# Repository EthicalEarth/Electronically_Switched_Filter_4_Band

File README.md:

This filter based on construction pu2clr from https://github.com/pu2clr/auto_bpf_arduino/ .

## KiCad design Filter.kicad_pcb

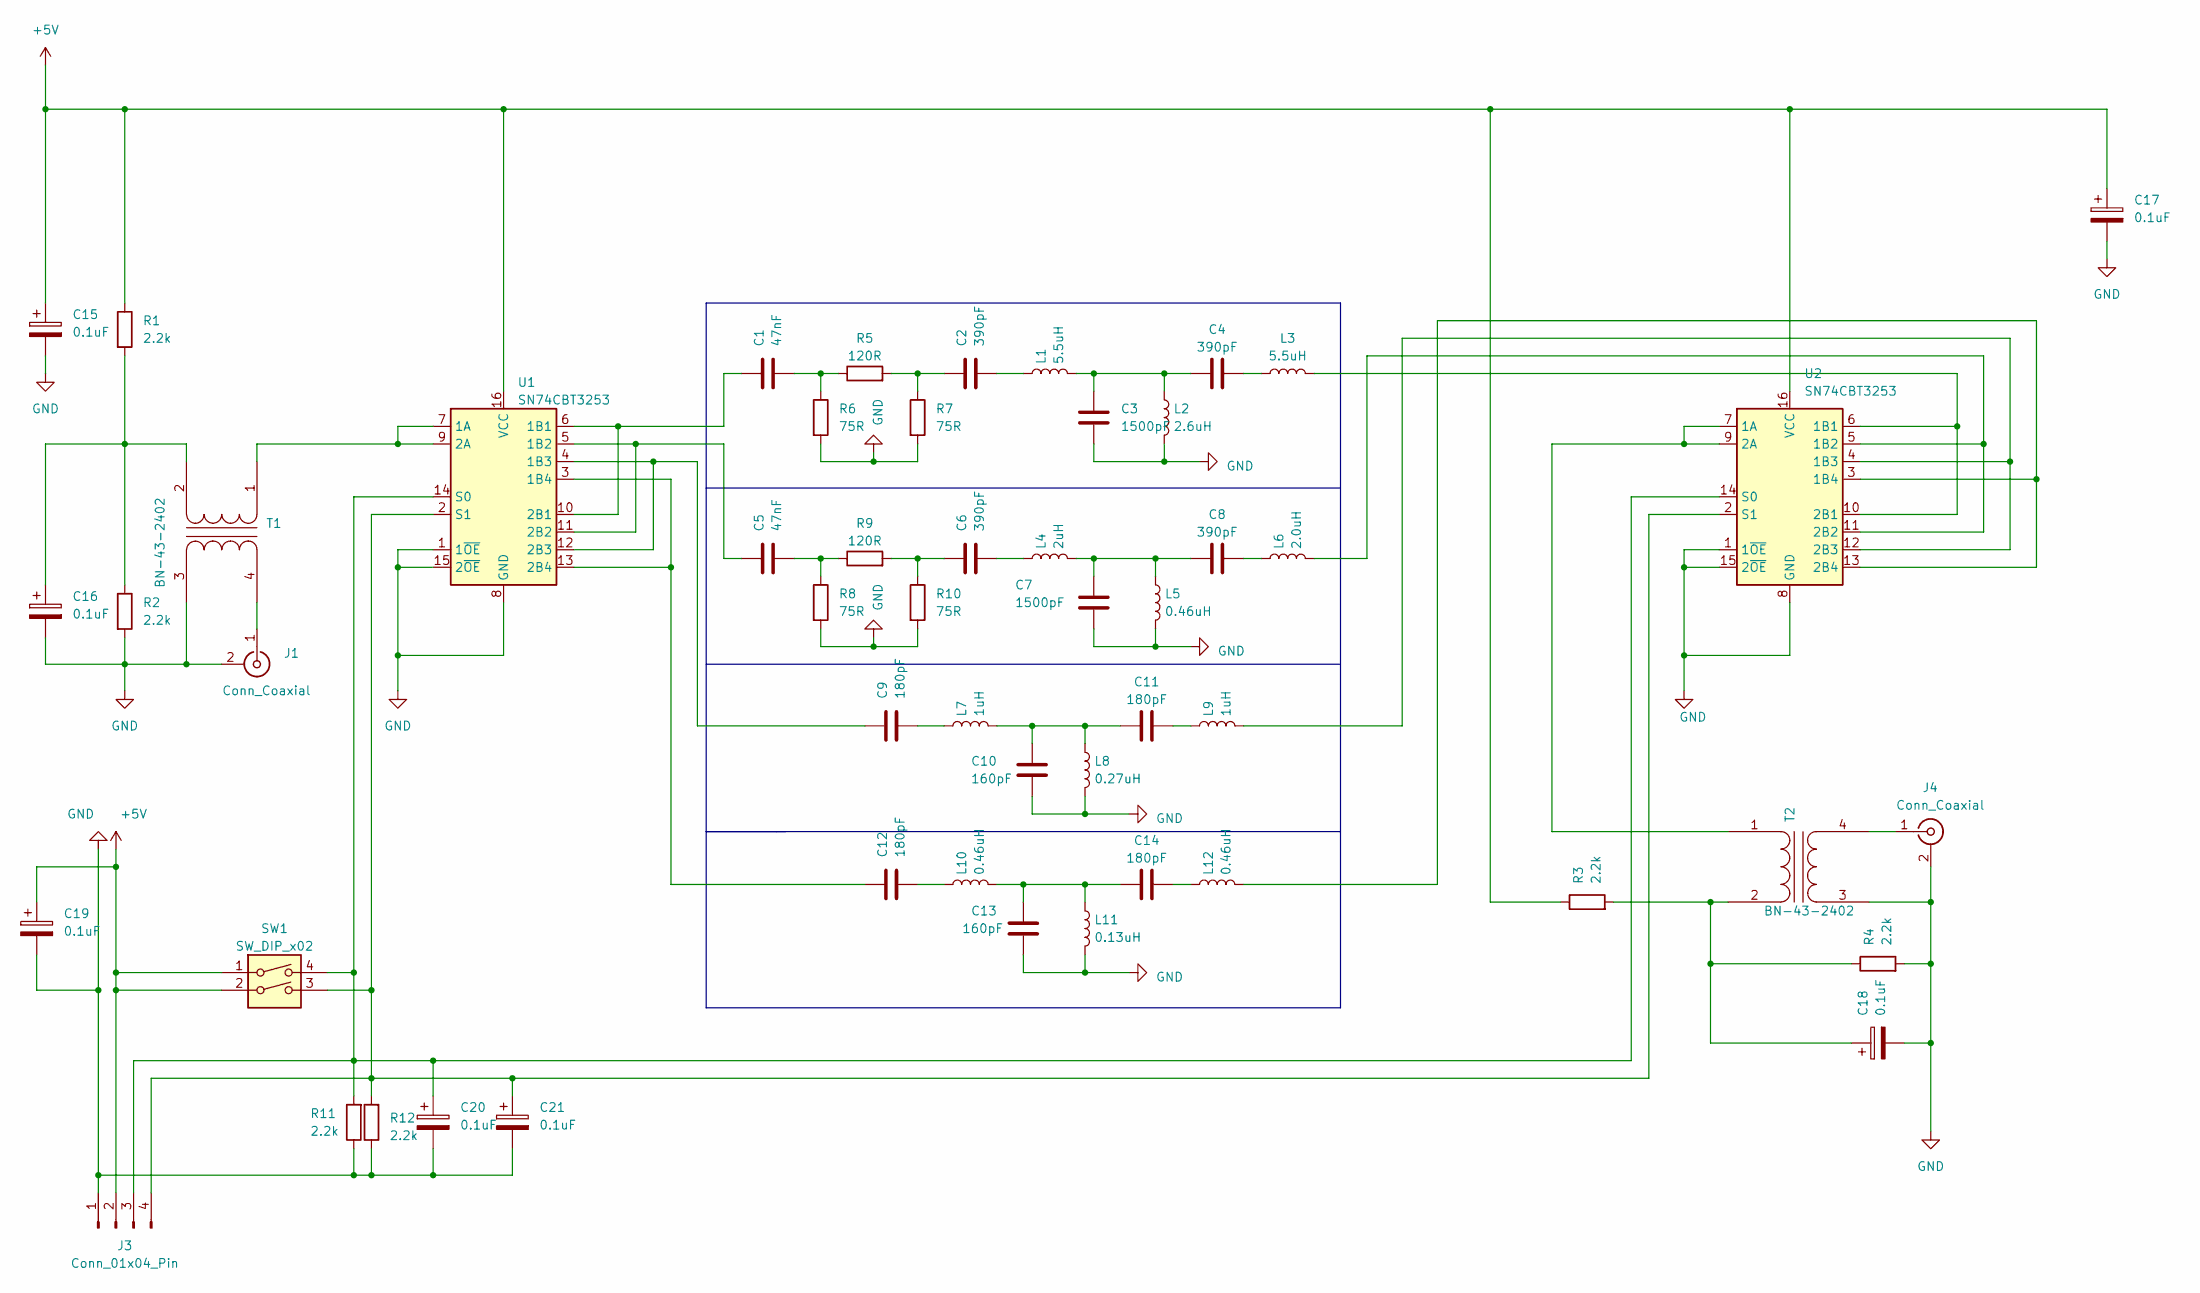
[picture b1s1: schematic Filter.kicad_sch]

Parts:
C1, C5: 47nF; C_Disc_D5.1mm_W3.2mm_P5.00mm
C2, C4, C6, C8: 390pF; C_Disc_D5.1mm_W3.2mm_P5.00mm
C3, C7: 1500pF; C_Disc_D5.1mm_W3.2mm_P5.00mm
C9, C11, C12, C14: 180pF; C_Disc_D5.1mm_W3.2mm_P5.00mm
C10, C13: 160pF; C_Disc_D5.1mm_W3.2mm_P5.00mm
C15, C16, C17, C18, C19, C20, C21: 0.1uF; C_1206_3216Metric
J1, J4: Conn_Coaxial; SMA_Amphenol_901-143_Horizontal
J3: Conn_01x04_Pin; PinSocket_1x04_P2.54mm_Vertical
L1, L3: 5.5uH; L_Toroid_Horizontal_D7.8mm_P13.00mm_Diameter9-5mm_Amidon-T30
L2: 2.6uH; L_Toroid_Horizontal_D7.8mm_P13.00mm_Diameter9-5mm_Amidon-T30
L4: 2uH; L_Toroid_Horizontal_D7.8mm_P13.00mm_Diameter9-5mm_Amidon-T30
L5: 0.46uH; L_Toroid_Horizontal_D7.8mm_P13.00mm_Diameter9-5mm_Amidon-T30
L6: 2.0uH; L_Toroid_Horizontal_D7.8mm_P13.00mm_Diameter9-5mm_Amidon-T30
L7, L9: 1uH; L_Toroid_Horizontal_D6.5mm_P10.00mm_Diameter7-5mm_Amidon-T25
L8: 0.27uH; L_Toroid_Horizontal_D6.5mm_P10.00mm_Diameter7-5mm_Amidon-T25
L10, L12: 0.46uH; L_Toroid_Horizontal_D6.5mm_P10.00mm_Diameter7-5mm_Amidon-T25
L11: 0.13uH; L_Toroid_Horizontal_D6.5mm_P10.00mm_Diameter7-5mm_Amidon-T25
R1, R2, R3, R4, R11, R12: 2.2k; R_1206_3216Metric
R5, R9: 120R; R_1206_3216Metric
R6, R7, R8, R10: 75R; R_1206_3216Metric
SW1: SW_DIP_x02; SW_DIP_SPSTx02_Slide_6.7x6.64mm_W8.61mm_P2.54mm_LowProfile
T1, T2: BN-43-2402; Transformer_Toroid_Horizontal_D9.0mm_Amidon-T30
U1, U2: SN74CBT3253; TSSOP-16_4.4x5mm_P0.65mm

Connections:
+5V: C15.1, C17.1, C19.1, J3.2, R1.1, R3.1, SW1.1, SW1.2, U1.16 (VCC), U2.16 (VCC)
GND: C3.2, C7.2, C10.2, C13.2, C15.2, C16.2, C17.2, C18.2, C19.2, C20.2, C21.2, J1.2 (Ext), J3.1, J4.2 (Ext), L2.2, L5.2, L8.2, L11.2, R2.2, R4.2, R6.2, R7.2, R8.2, R10.2, R11.1, R12.1, T1.3 (SA), T2.3 (SA), U1.1 (1~OE), U1.8 (GND), U1.15 (2~OE), U2.1 (1~OE), U2.8 (GND), U2.15 (2~OE)
unnamed: C1.2, R5.1, R6.1
unnamed: C2.1, R5.2, R7.1
unnamed: C2.2, L1.1
unnamed: C3.1, C4.1, L1.2, L2.1
unnamed: C4.2, L3.1
unnamed: C5.2, R8.1, R9.1
unnamed: C6.1, R9.2, R10.1
unnamed: C6.2, L4.1
unnamed: C7.1, C8.1, L4.2, L5.1
unnamed: C8.2, L6.1
unnamed: C9.2, L7.1
unnamed: C10.1, C11.1, L7.2, L8.1
unnamed: C11.2, L9.1
unnamed: C12.2, L10.1
unnamed: C13.1, C14.1, L10.2, L11.1
unnamed: C14.2, L12.1
unnamed: J1.1 (In), T1.4 (SB)
unnamed: C20.1, J3.3, R11.2, SW1.4, U1.14 (S0), U2.14 (S0)
unnamed: C21.1, J3.4, R12.2, SW1.3, U1.2 (S1), U2.2 (S1)
unnamed: J4.1 (In), T2.4 (SB)
unnamed: T1.1 (AA), U1.7 (1A), U1.9 (2A)
unnamed: C16.1, R1.2, R2.1, T1.2 (AB)
unnamed: T2.1 (AA), U2.7 (1A), U2.9 (2A)
unnamed: C18.1, R3.2, R4.1, T2.2 (AB)
unnamed: C1.1, U1.6 (1B1), U1.10 (2B1)
unnamed: C5.1, U1.5 (1B2), U1.11 (2B2)
unnamed: C9.1, U1.4 (1B3), U1.12 (2B3)
unnamed: C12.1, U1.3 (1B4), U1.13 (2B4)
unnamed: L3.2, U2.6 (1B1), U2.10 (2B1)
unnamed: L6.2, U2.5 (1B2), U2.11 (2B2)
unnamed: L9.2, U2.4 (1B3), U2.12 (2B3)
unnamed: L12.2, U2.3 (1B4), U2.13 (2B4)

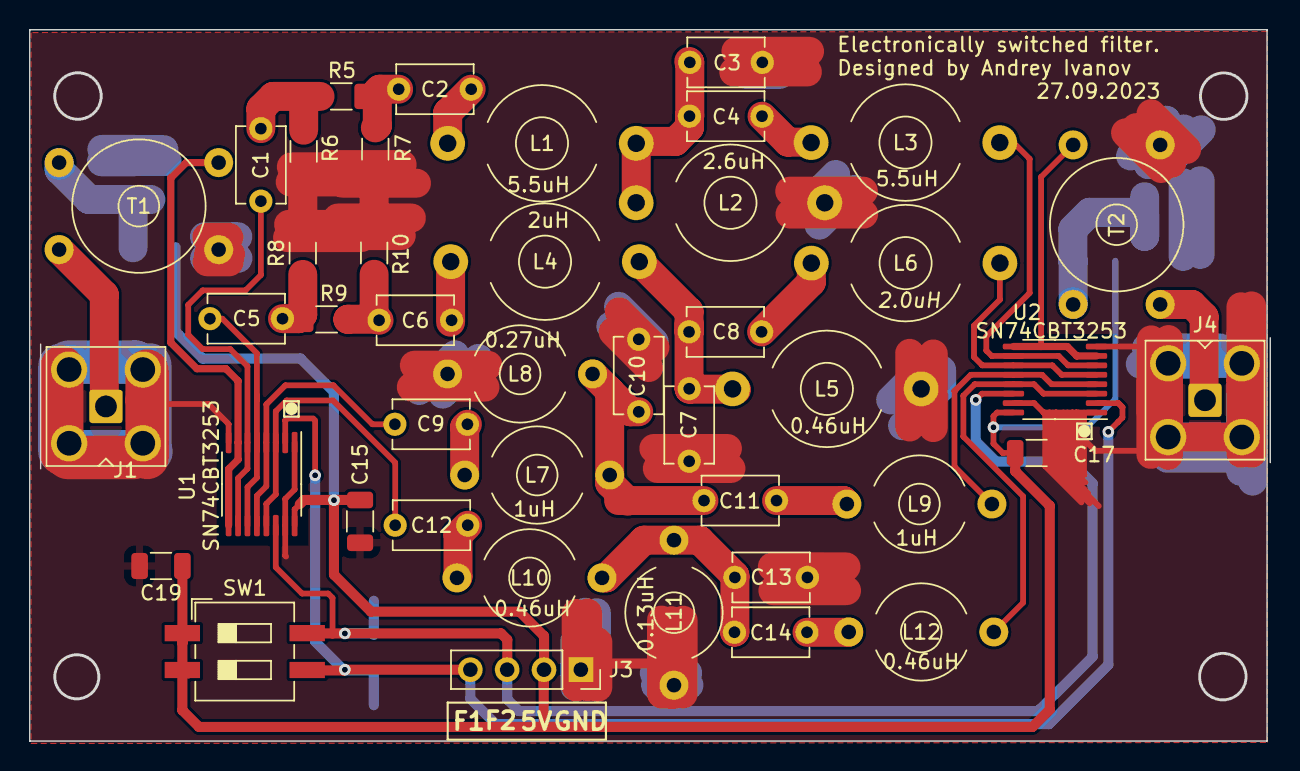
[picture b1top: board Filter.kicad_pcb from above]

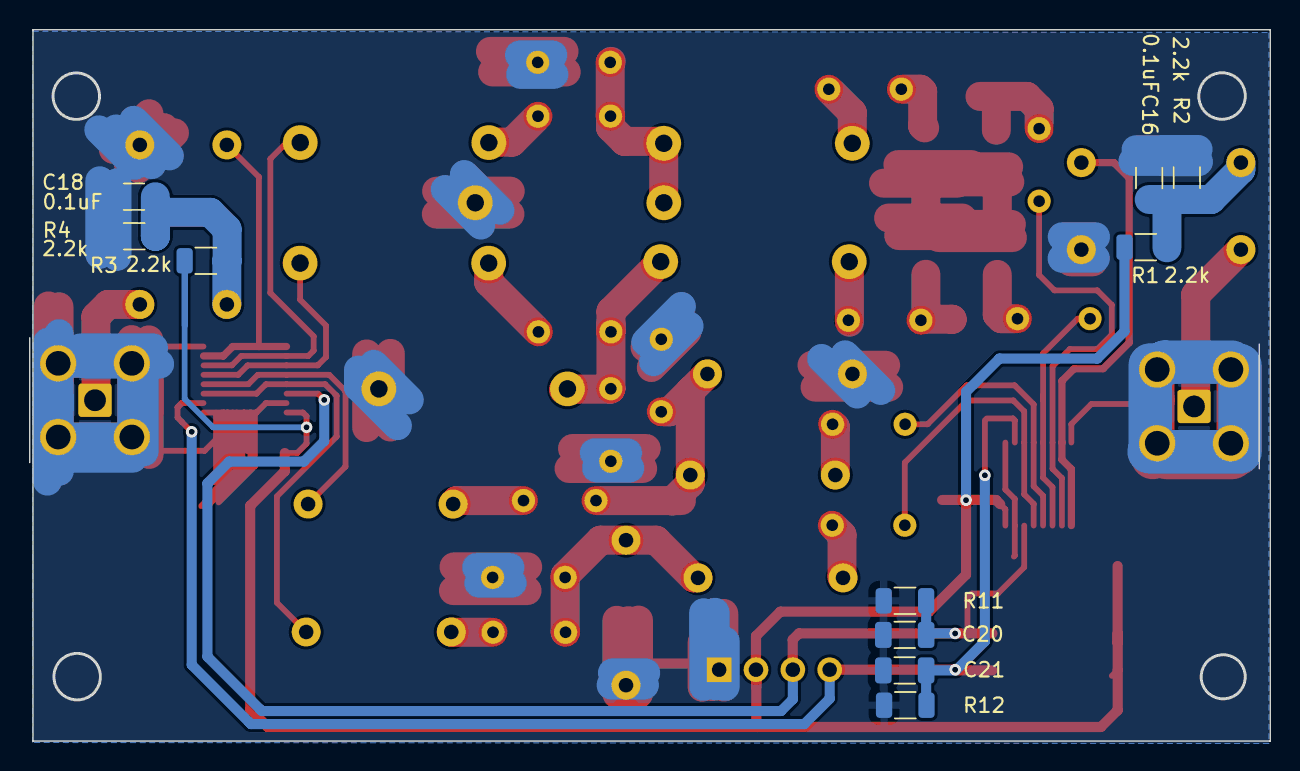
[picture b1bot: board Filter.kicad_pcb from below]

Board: 2 copper layers, 85.3 x 49.0 mm, 53 parts (10 on the bottom side), 34 nets.

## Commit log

2023-11-05 Init
2023-11-10 Changes.
2024-03-23 Correcting the project,cirquits and board
2024-03-23 Correctig Gerber files
